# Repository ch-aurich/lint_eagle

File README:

LINT for EAGLE XML Files
========================

This project aims to check eagle files for good style. It checks that you use eagle in a sane way instead stressing your luck and hoping that everything will be ok.

Installation
============

TBD

Usage
=====

TBD

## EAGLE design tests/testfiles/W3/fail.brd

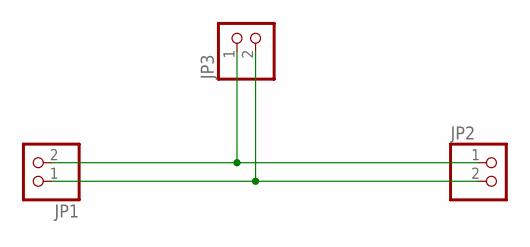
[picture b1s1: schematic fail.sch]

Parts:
JP1, JP2, JP3: PINHD-1X2; 1X02

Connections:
unnamed: JP1.2, JP2.1, JP3.1
unnamed: JP1.1, JP2.2, JP3.2

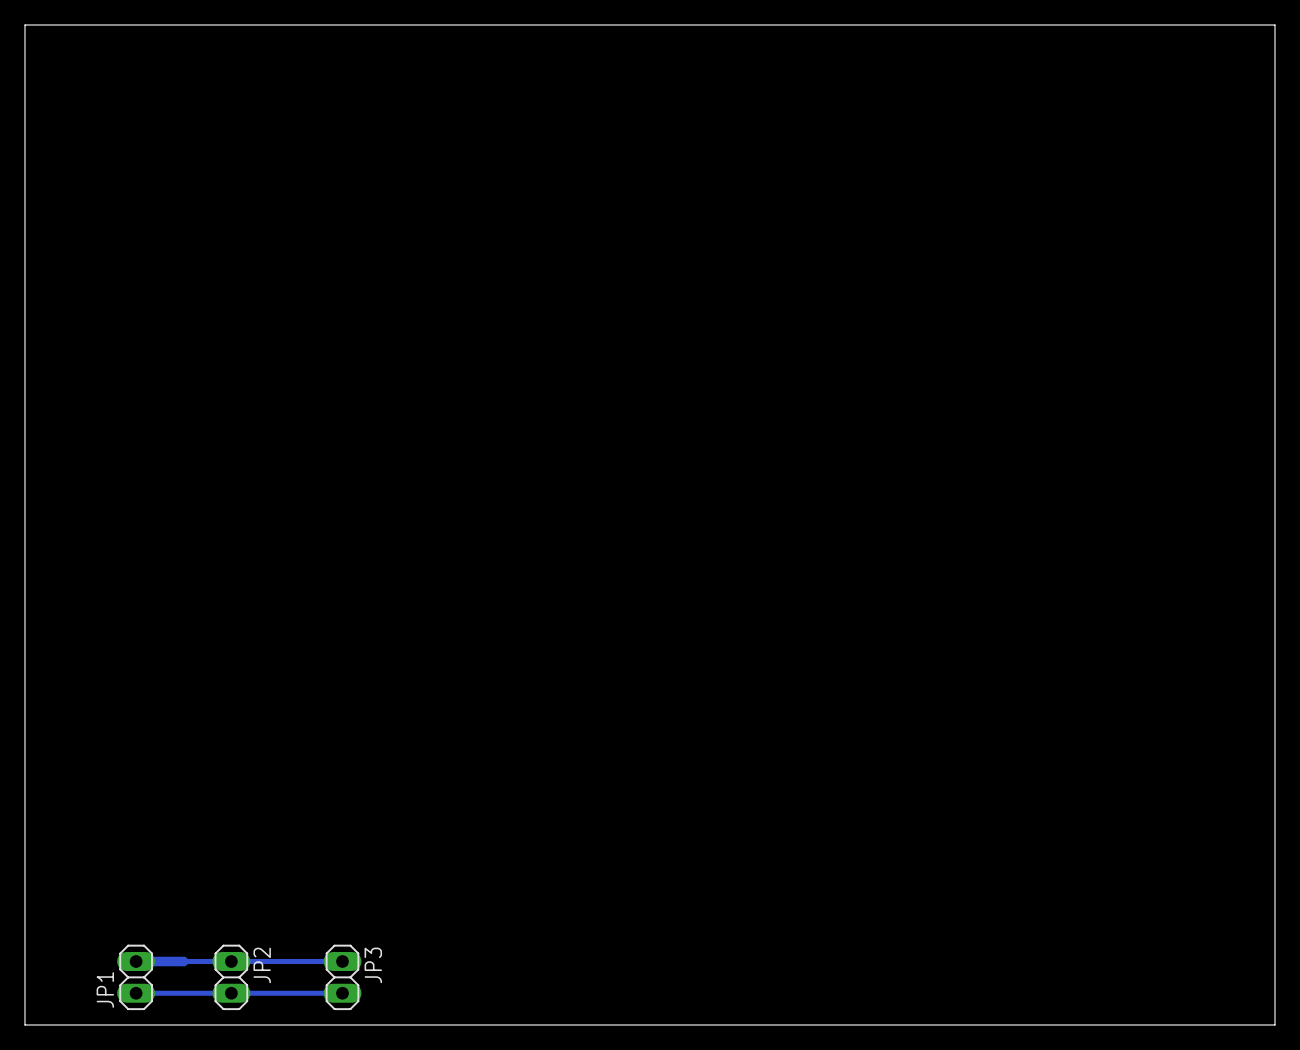
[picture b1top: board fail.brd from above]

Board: 2 copper layers, 100.0 x 80.0 mm, 3 parts (0 on the bottom side), 2 nets.

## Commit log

2014-05-08 initial commit of a basic set of tests and a rudimentary command line interface implementation
2014-05-09 adding .travis.yml for automated tests
2014-05-09 changing name of test folder from "test" to "tests" in the travis config
2014-05-09 making the first test that was already coded available through the command line tool...
2014-09-30 updating list of checks: separated tName and tValue issues...
2014-09-30 - adding a generic class for all issues within lint_eagle - modified implementation of library check for tName and tValue to match with ne generic issue class - added check for correct layer of tName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
2014-10-01 making lint_eagle.py compatible with changed method name of eagle_lbr.py
2014-10-01 fixing indent (return was in for loop)
2014-10-01 making lbr check failsave if it gets a brd object passed
2014-10-01 implementing a check for testpads in a board
2014-10-01 improving output formatting
2014-10-01 improving failure handling if library package does not contain any text at all (expect >NAME and >VALUE here)
2014-10-23 adding testfiles for issues #1 and #2
2015-04-18 fixing issue #1
2015-05-27 this commit patches a problem where signals without a contactref (this can be cutout polygons) caused the script to crash. The testpad check is skipped for such "signals" now.
2015-05-27 adding return value, 0=success, 1=some not suppressed issues were found
